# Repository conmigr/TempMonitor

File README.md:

# TempMonitor
Open temperature monitoring raw pcb designed to use the MCP 9808 tempreture chip.

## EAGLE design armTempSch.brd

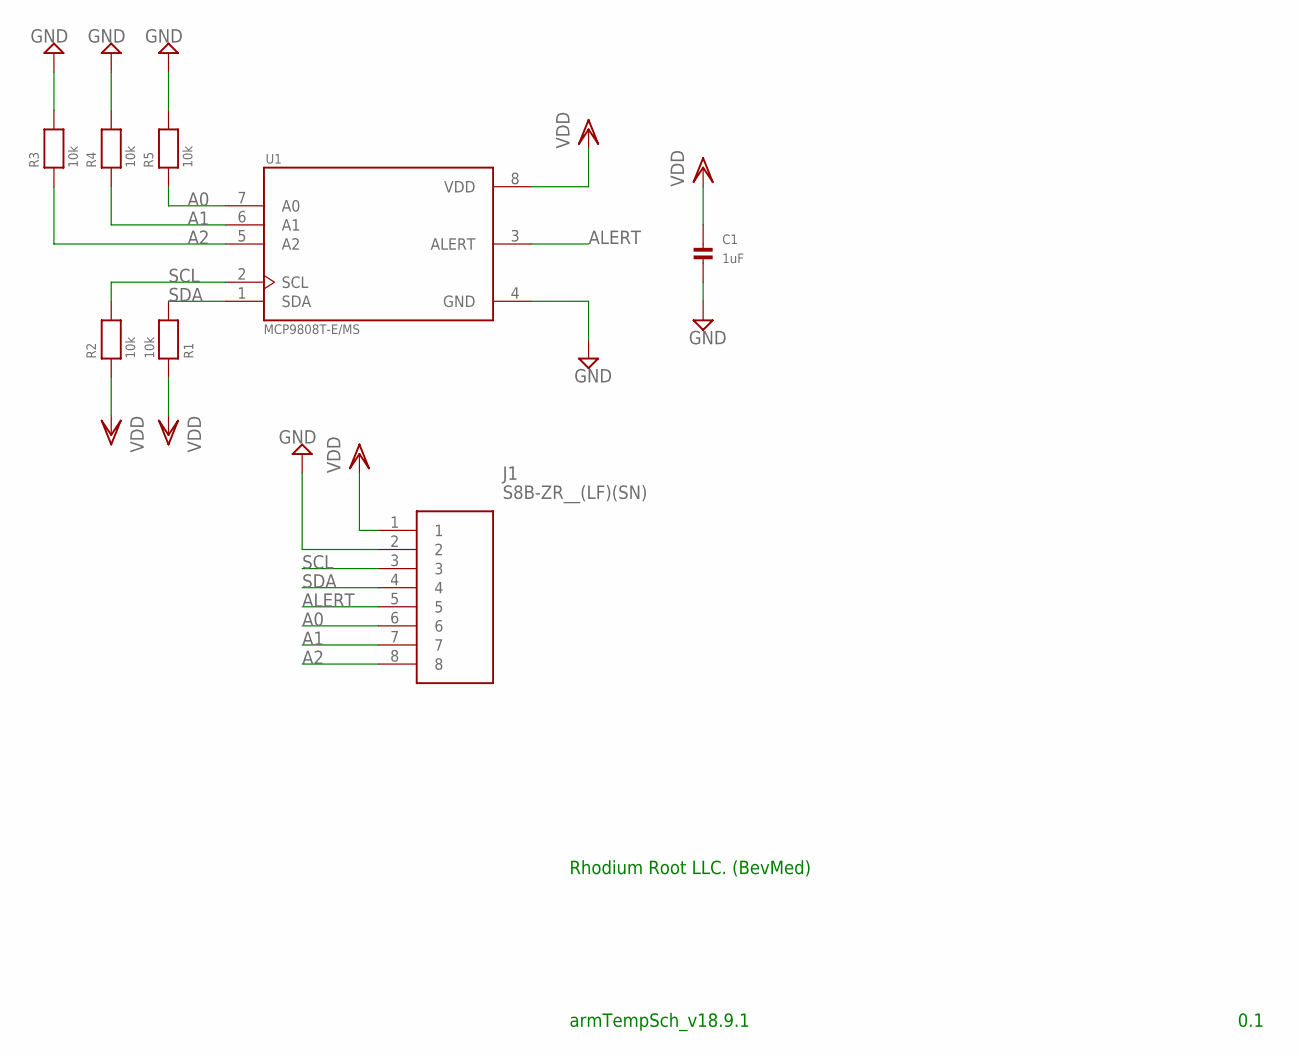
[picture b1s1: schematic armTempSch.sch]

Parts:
C1: 1uF; _0805; MPN MCTT21X105K160CT
J1: S8B-ZR__(LF)(SN); SHDR8W50P0X150_1X8_1350X600X37; MPN S8B-ZR
R1, R2, R3, R4, R5: 10k; 0805; MPN ERJ-6GEYJ103V
U1: MCP9808T-E/MS; SOP65P490X110-8N; MPN MCP9808T-E/MS

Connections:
A0: J1.6, R5.1, U1.7 (A0)
A1: J1.7, R4.1, U1.6 (A1)
A2: J1.8, R3.1, U1.5 (A2)
ALERT: J1.5, U1.3 (ALERT)
GND: C1.2, J1.2, R3.2, R4.2, R5.2, U1.4 (GND)
SCL: J1.3, R2.2, U1.2 (SCL)
SDA: J1.4, R1.2, U1.1 (SDA)
VDD: C1.1, J1.1, R1.1, R2.1, U1.8 (VDD)

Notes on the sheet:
0.1
armTempSch_v18.9.1
Rhodium Root LLC. (BevMed)

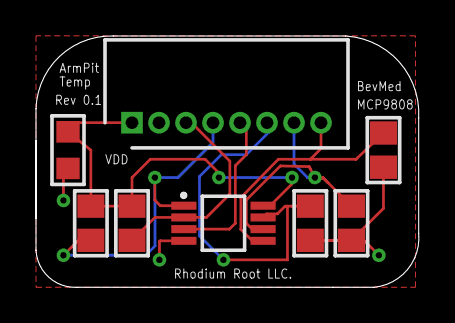
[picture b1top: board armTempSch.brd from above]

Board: 2 copper layers, 21.3 x 14.0 mm, 8 parts (0 on the bottom side), 8 nets.

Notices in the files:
parts and their libraries:
microbuilder: This work is placed in the public domain, and may be freely used for commercial and non-commercial work with the following conditions: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
